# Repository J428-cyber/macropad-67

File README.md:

# Macropad-67

A compact custom macropad designed for learning and experimentation in PCB design and CAD.

## Tools Used

* **KiCad** – schematic capture, PCB layout, and 3D PCB visualization
* **Onshape** – enclosure and mechanical CAD design

## Project Overview

* Custom PCB designed in KiCad
* Custom footprints used for components
* Enclosure modeled and assembled in Onshape
* Intended as a beginner-to-intermediate hardware project

## Images

**PCB Footprint**

**PCB 3D View**

**CAD Assembly**

## Status

Hardware design complete. Firmware and testing in progress.

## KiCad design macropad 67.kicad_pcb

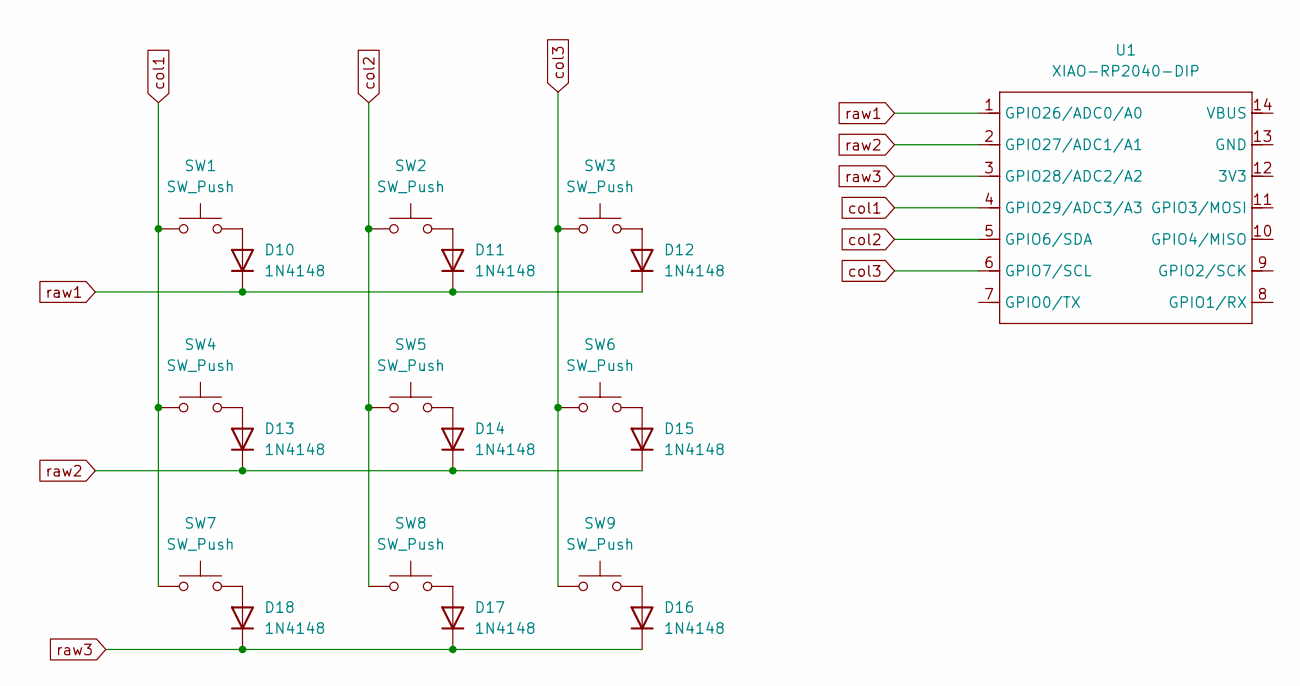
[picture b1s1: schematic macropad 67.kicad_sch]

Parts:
D10, D11, D12, D13, D14, D15, D16, D17, D18: 1N4148; D_DO-35_SOD27_P7.62mm_Horizontal
SW1, SW2, SW3, SW4, SW5, SW6, SW7, SW8, SW9: SW_Push; SW_Cherry_MX_1.00u_PCB
U1: XIAO-RP2040-DIP

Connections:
unnamed: D10.2 (A), SW1.2
unnamed: D11.2 (A), SW2.2
unnamed: D12.2 (A), SW3.2
unnamed: D13.2 (A), SW4.2
unnamed: D14.2 (A), SW5.2
unnamed: D15.2 (A), SW6.2
unnamed: D16.2 (A), SW9.2
unnamed: D17.2 (A), SW8.2
unnamed: D18.2 (A), SW7.2
col1: SW1.1, SW4.1, SW7.1, U1.4 (GPIO29/ADC3/A3)
col2: SW2.1, SW5.1, SW8.1, U1.5 (GPIO6/SDA)
col3: SW3.1, SW6.1, SW9.1, U1.6 (GPIO7/SCL)
raw1: D10.1 (K), D11.1 (K), D12.1 (K), U1.1 (GPIO26/ADC0/A0)
raw2: D13.1 (K), D14.1 (K), D15.1 (K), U1.2 (GPIO27/ADC1/A1)
raw3: D16.1 (K), D17.1 (K), D18.1 (K), U1.3 (GPIO28/ADC2/A2)

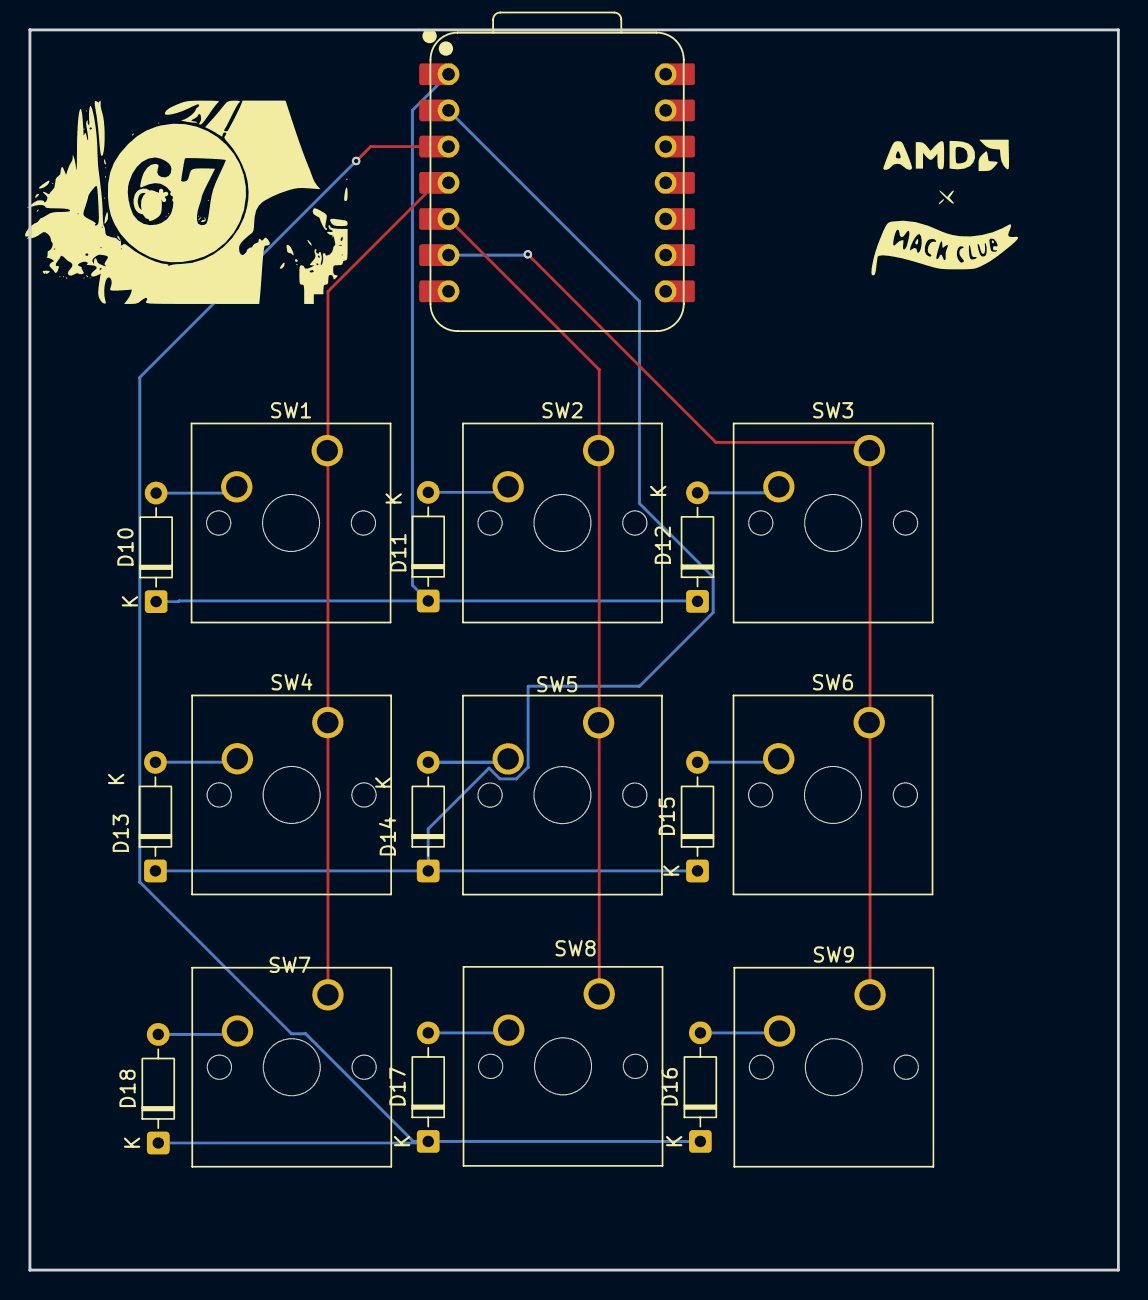
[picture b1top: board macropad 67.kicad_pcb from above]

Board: 2 copper layers, 76.4 x 87.0 mm, 19 parts (0 on the bottom side), 15 nets.

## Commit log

2026-01-05 Create macropad67 pcb
2026-01-05 cad files upload
2026-01-05 Add images section to README
